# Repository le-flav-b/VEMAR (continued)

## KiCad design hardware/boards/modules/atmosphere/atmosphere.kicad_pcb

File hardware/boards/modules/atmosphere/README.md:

description of the board, maybe advice or intructions

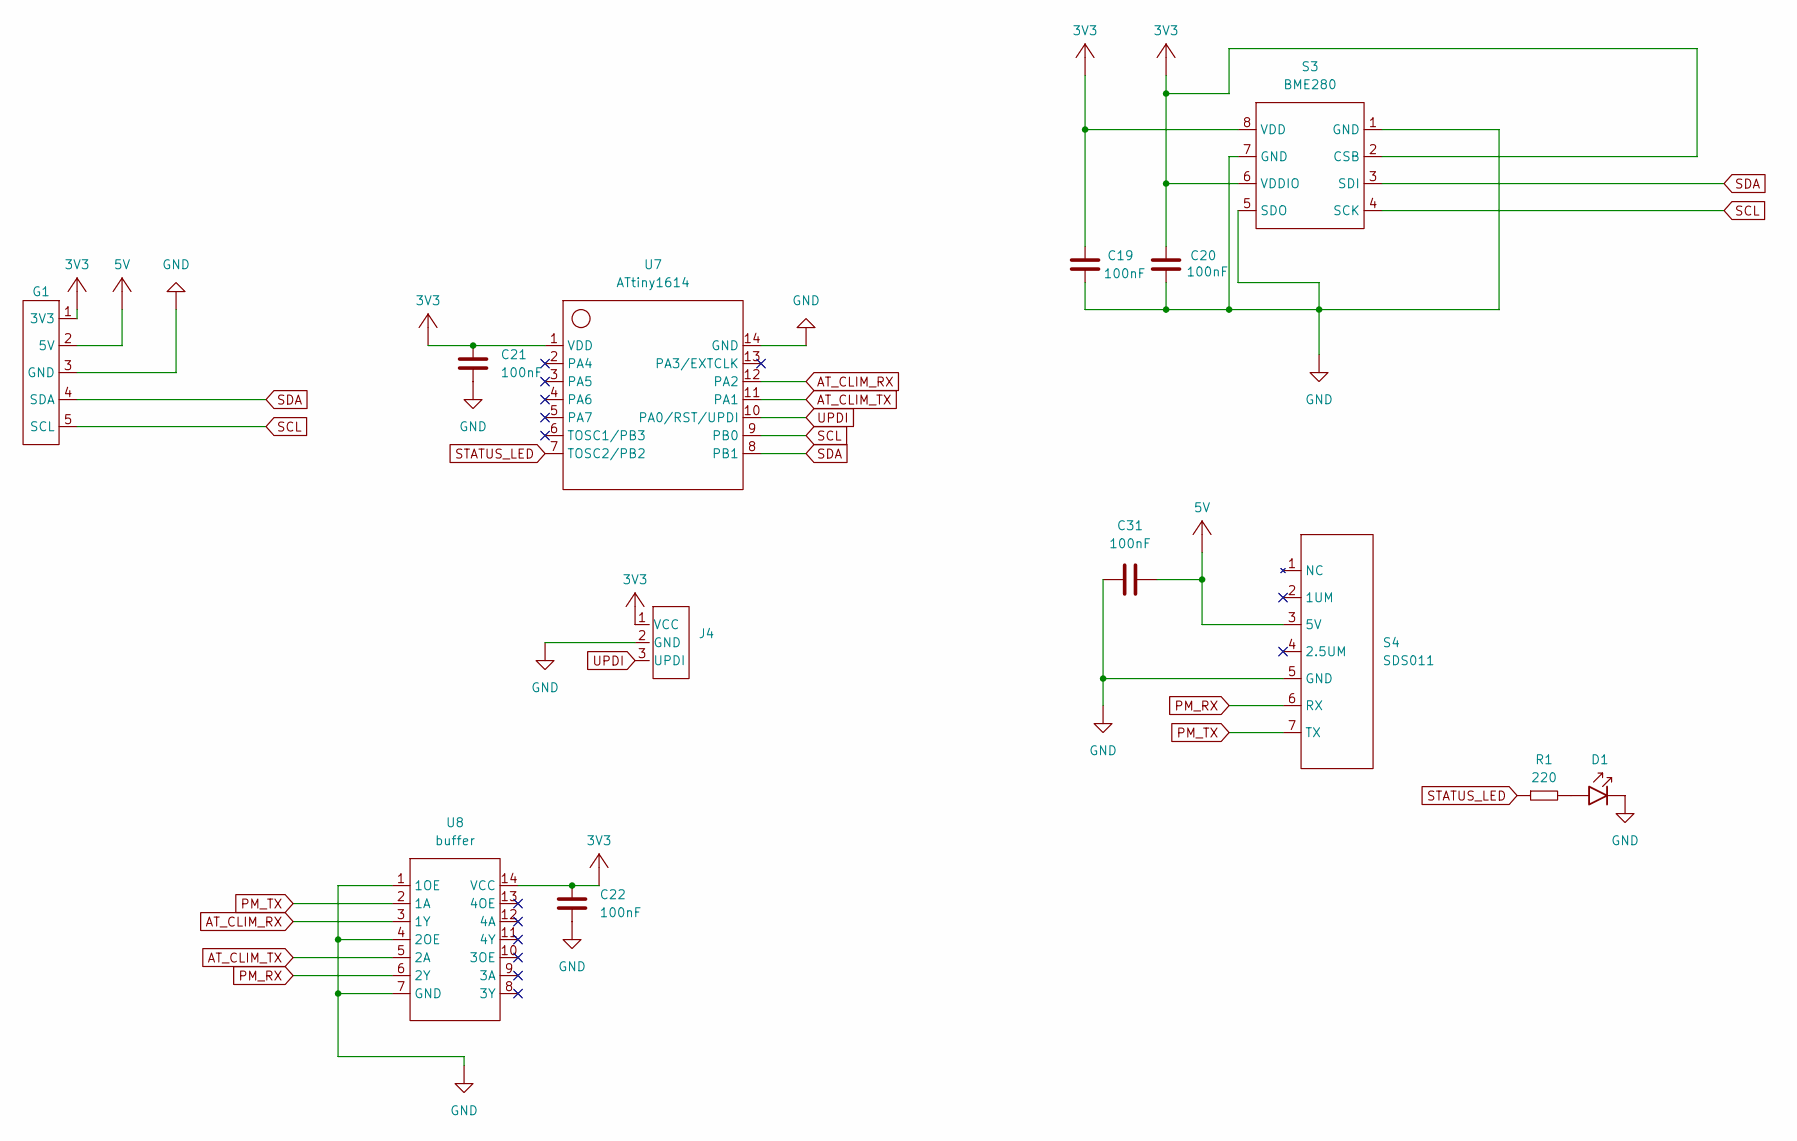
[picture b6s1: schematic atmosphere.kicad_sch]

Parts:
C19, C20, C21, C22, C31: 100nF; C_0603
D1: LED_3mm_THT
G1: GPIO_HEADER
J4: ATtiny_Programming_Header
R1: 220; R_0603
S3: BME280
S4: SDS011
U7: ATtiny1614
U8: buffer; SN74LVC125

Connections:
3V3: C19.1, C20.2, C21.2, C22.2, G1.1 (3V3), J4.1 (VCC), S3.2 (CSB), S3.6 (VDDIO), S3.8 (VDD), U7.1 (VDD), U8.14 (VCC)
5V: C31.2, G1.2 (5V), S4.3 (5V)
AT_CLIM_RX: U7.12 (PA2), U8.3 (1Y)
AT_CLIM_TX: U7.11 (PA1), U8.5 (2A)
GND: C19.2, C20.1, C21.1, C22.1, C31.1, D1.1 (K), G1.3 (GND), J4.2 (GND), S3.1 (GND), S3.5 (SDO), S3.7 (GND), S4.5 (GND), U7.14 (GND), U8.1 (1OE), U8.4 (2OE), U8.7 (GND)
unnamed: D1.2 (A), R1.2
PM_RX: S4.6 (RX), U8.6 (2Y)
PM_TX: S4.7 (TX), U8.2 (1A)
SCL: G1.5 (SCL), S3.4 (SCK), U7.9 (PB0)
SDA: G1.4 (SDA), S3.3 (SDI), U7.8 (PB1)
STATUS_LED: R1.1, U7.7 (TOSC2/PB2)
UPDI: J4.3 (UPDI), U7.10 (PA0/RST/UPDI)

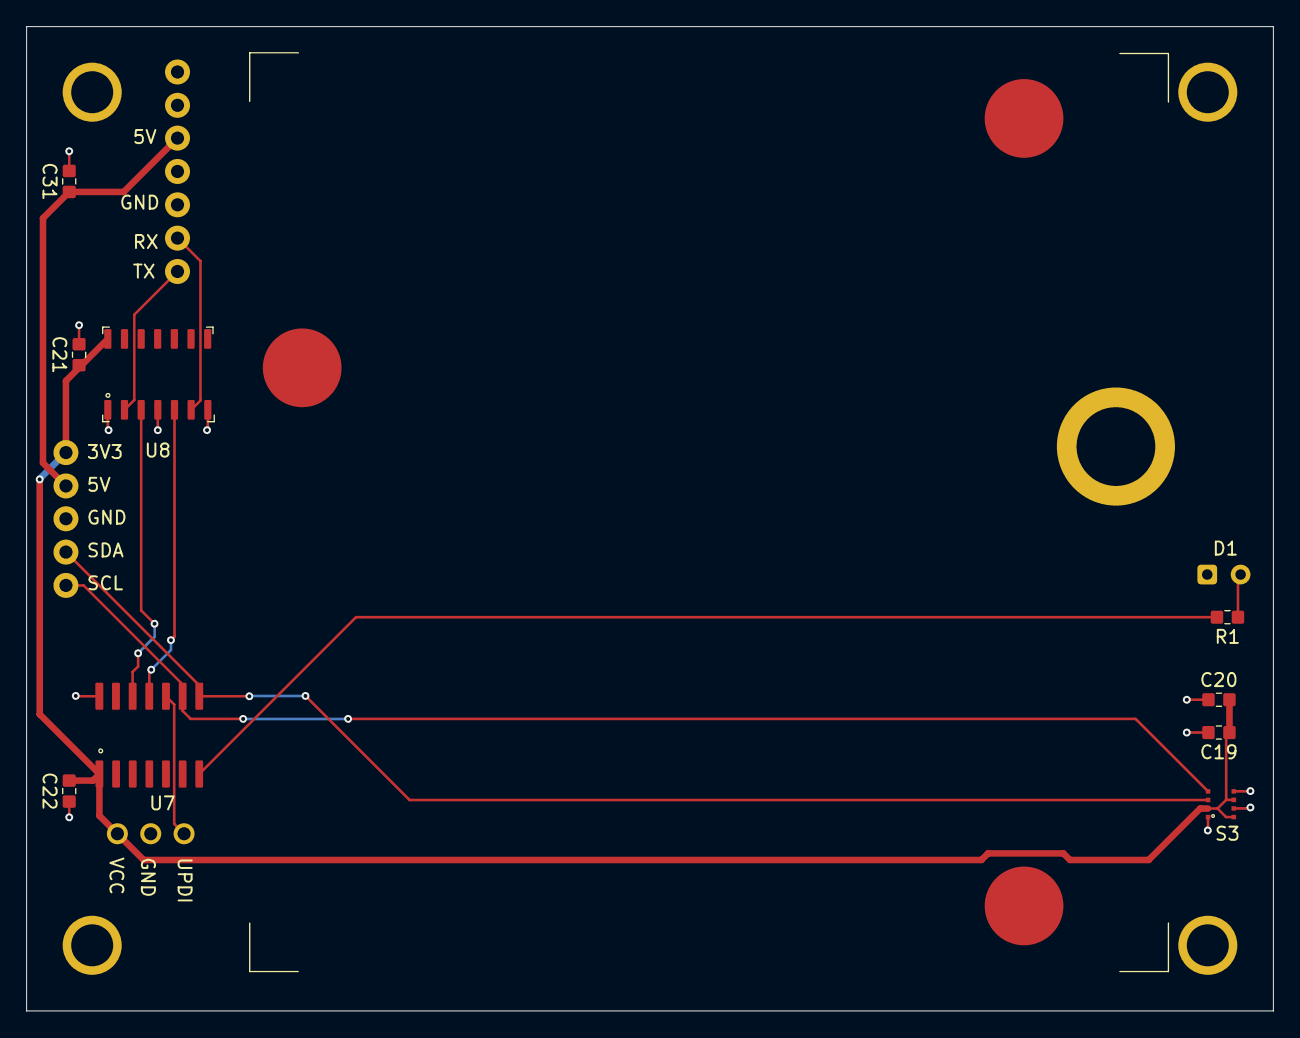
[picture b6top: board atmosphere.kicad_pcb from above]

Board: 2 copper layers, 95.0 x 75.0 mm, 13 parts (0 on the bottom side), 12 nets.

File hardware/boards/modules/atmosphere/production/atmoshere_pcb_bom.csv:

Designator,Footprint,Quantity,Value,LCSC Part #
"C19, C20, C21, C22, C31",C_0603,5,100nF,
D1,LED_3mm_THT,1,~,
G1,GPIO_HEADER,1,~,
J4,ATtiny_Programming_Header,1,~,
R1,R_0603,1,220,
S3,BME280,1,BME280,
S4,SDS011,1,SDS011,
U7,ATtiny1614,1,ATtiny1614,
U8,SN74LVC125,1,buffer,

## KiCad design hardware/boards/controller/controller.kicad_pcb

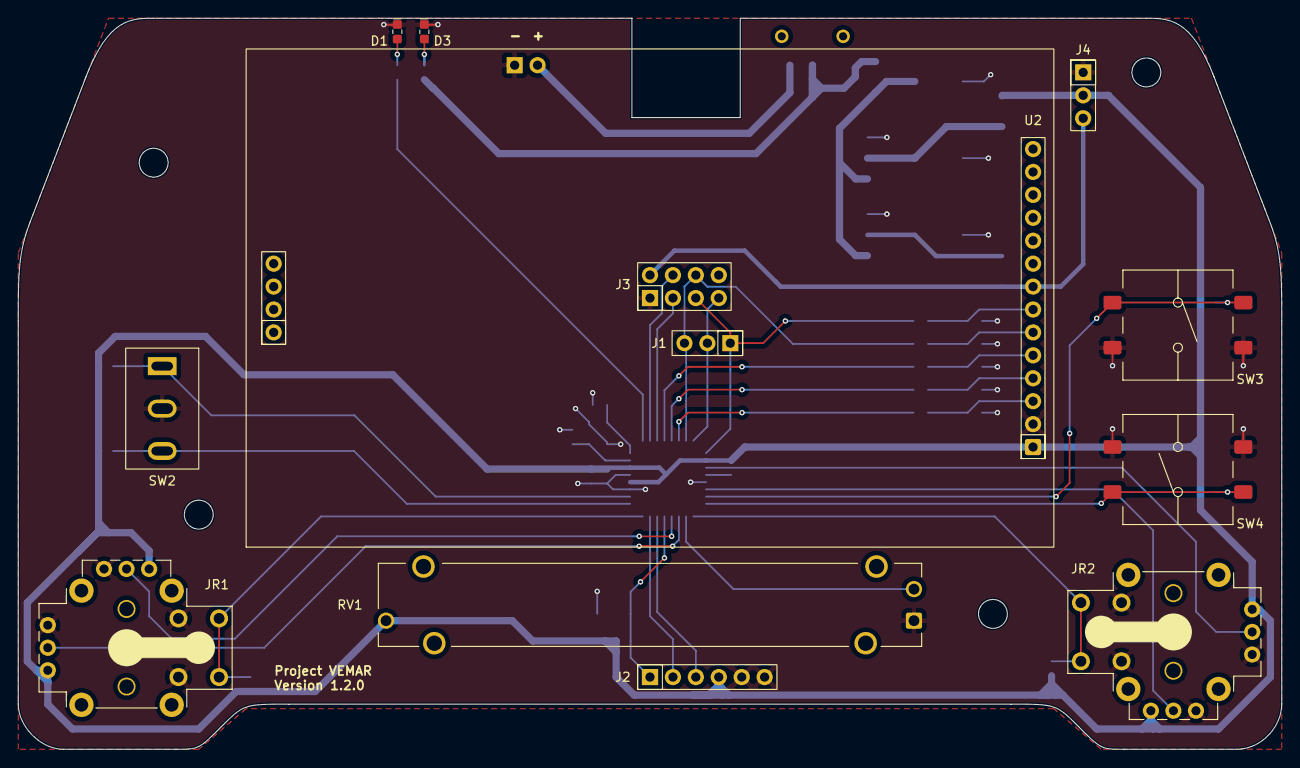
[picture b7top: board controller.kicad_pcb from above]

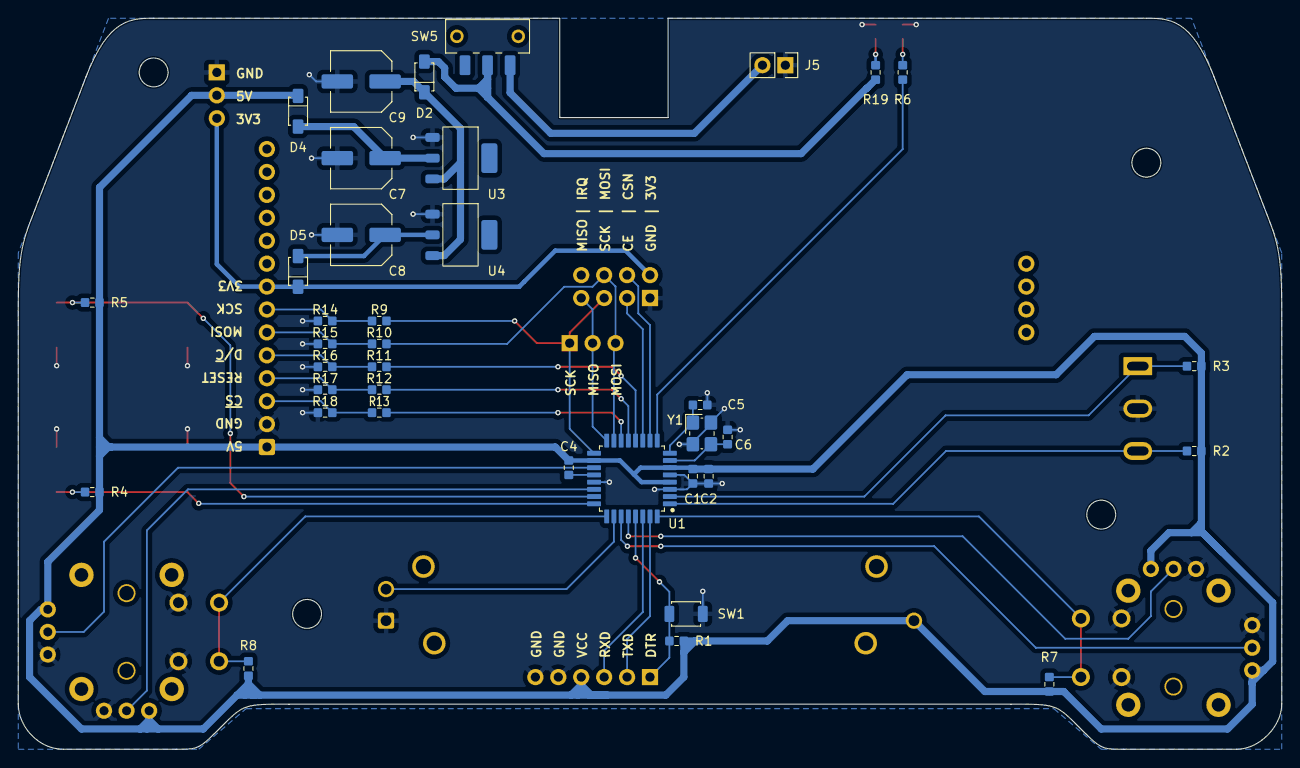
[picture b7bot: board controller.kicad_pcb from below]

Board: 2 copper layers, 140.0 x 81.0 mm, 50 parts (37 on the bottom side), 41 nets.

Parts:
C1: 1uF; C_0603
C2, C4: 100nF; C_0603
C5, C6: 12pF; C_0603
C7, C8: 22uF; C_D6.3xL5.4
C9: 100uF; C_D6.3xL5.4
D1: Green; LED_0603
D2, D4, D5: Diode; D_SOD123FL
D3: Red; LED_0603
J1, J4: 01x03; Pin_01x03
J2: 01x06; Pin_01x06
J3: 02x04; Pin_02x04
J5: 01x02; Pin_01x02
JR1, JR2: Joystick
R1, R2, R3, R4, R5, R7, R8: 10k; R_0603
R6: 330; R_0603
R9, R10, R11, R12, R13, R19: 1k; R_0603
R14, R15, R16, R17, R18: 2k; R_0603
RV1: Potentiometer; RV_45
SW1: Reset; SW_Tactile3x2.5
SW2: SW_SPDT; SW_Toggle
SW3, SW4: SW; SW_Tactile12x12
SW5: Power; SW_Slide9.1x3.5
U1: ATmega328P; ATmega328p_TQFP
U2: ILI9341
U3: AMS1117-5.0; AMS1117-SOT223
U4: AMS1117-3.3; AMS1117-SOT223
Y1: 16MHz; Crystal_3225

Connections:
+3.3V: D5.1 (K), J3.8, J4.3, U2.8 (LED)
+5V: C1.2, C2.2, C4.1, D4.1 (K), J2.4, J4.2, JR1.1 (VCC), JR1.4 (VCC), JR2.1 (VCC), JR2.4 (VCC), R1.2, R2.2, R3.2, R4.2, R5.2, R7.1, R8.2, RV1.3, U1.4 (VCC), U1.6 (VCC), U1.18 (AVCC), U2.1 (VCC)
+BATTERY: C9.1, D2.1 (K), U3.3 (VIN), U4.3 (VIN)
BTN1: R5.1, SW3.1, SW3.2, U1.23 (PC0/ADC0/PCINT8)
BTN2: R4.1, SW4.1, SW4.2, U1.24 (PC1/ADC1/PCINT9)
CE: J3.2, U1.11 (PCINT23/AIN1/PD7)
CS: R13.2, U1.14 (PCINT2/~SS/OC1B/PB2)
CSN: J3.7, U1.10 (PCINT22/OC0A/AIN0/PD6)
DC: R11.2, U1.12 (PCINT0/CLKO/ICP1/PB0)
DTR: J2.1, R1.1, SW1.2, U1.29 (PC6/~RESET/PCINT14)
GND: C1.1, C2.1, C5.1, C6.1, C7.2, C8.2, C9.2, D1.1 (K), D3.1 (K), J2.5, J2.6, J3.1, J4.1, J5.1, JR1.3 (GND), JR1.6 (GND), JR1.8 (SW2), JR1.10 (SW2), JR2.3 (GND), JR2.6 (GND), JR2.8 (SW2), JR2.10 (SW2), R14.1, R15.1, R16.1, R17.1, R18.1, RV1.1, SW1.1, SW2.2, SW3.3, SW3.4, SW4.3, SW4.4, U1.3 (GND), U1.5 (GND), U1.21 (GND), U2.2 (GND), U3.1 (GND), U4.1 (GND), Y1.2 (GND), Y1.4 (GND)
JOY1-B: JR1.7 (SW1), JR1.9 (SW1), R7.2, U1.32 (INT0/PCINT18/PD2)
JOY1-X: JR1.5 (VR2), U1.27 (PC4/ADC4/SDA/PCINT12)
JOY1-Y: JR1.2 (VR1), U1.28 (PC5/ADC5/SCL/PCINT13)
JOY2-B: JR2.7 (SW1), JR2.9 (SW1), R8.1, U1.25 (PC2/ADC2/PCINT10)
JOY2-X: JR2.2 (VR1), U1.22 (ADC7)
JOY2-Y: JR2.5 (VR2), U1.19 (ADC6)
LED: R6.2, U1.9 (PCINT21/OC0B/T1/PD5)
MISO: J1.2, J3.4, U1.16 (PCINT4/MISO/PB4)
MOSI: J1.3, J3.6, R10.2, U1.15 (PCINT3/OC2A/MOSI/PB3)
unnamed: D1.2 (A), R6.1
unnamed: D2.2 (A), R19.2, SW5.2
unnamed: D3.2 (A), R19.1
unnamed: C7.1, D4.2 (A), U3.2 (VOUT)
unnamed: C8.1, D5.2 (A), U4.2 (VOUT)
unnamed: J5.2, SW5.3
unnamed: C4.2, U1.20 (AREF)
unnamed: RV1.2, U1.26 (PC3/ADC3/PCINT11)
unnamed: C6.2, U1.7 (PCINT6/XTAL1/TOSC1/PB6), Y1.3
unnamed: C5.2, U1.8 (PCINT7/XTAL2/TOSC2/PB7), Y1.1
unnamed: R11.1, R16.2, U2.5 (D/~C)
unnamed: R10.1, R15.2, U2.6 (MOSI)
unnamed: R12.1, R17.2, U2.4 (RESET)
unnamed: R9.1, R14.2, U2.7 (SCK)
unnamed: R13.1, R18.2, U2.3 (~CS)
RESET: R12.2, U1.13 (PCINT1/OC1A/PB1)
RXD: J2.3, U1.30 (RXD/PCINT16/PD0)
SCK: J1.1, J3.3, R9.2, U1.17 (SCK/PCINT5/PB5)
TOGGLE1: R2.1, SW2.3, U1.1 (PCINT19/OC2B/INT1/PD3)
TOGGLE2: R3.1, SW2.1, U1.2 (PCINT20/XCK/T0/PD4)
TXD: J2.2, U1.31 (TXD/PCINT17/PD1)

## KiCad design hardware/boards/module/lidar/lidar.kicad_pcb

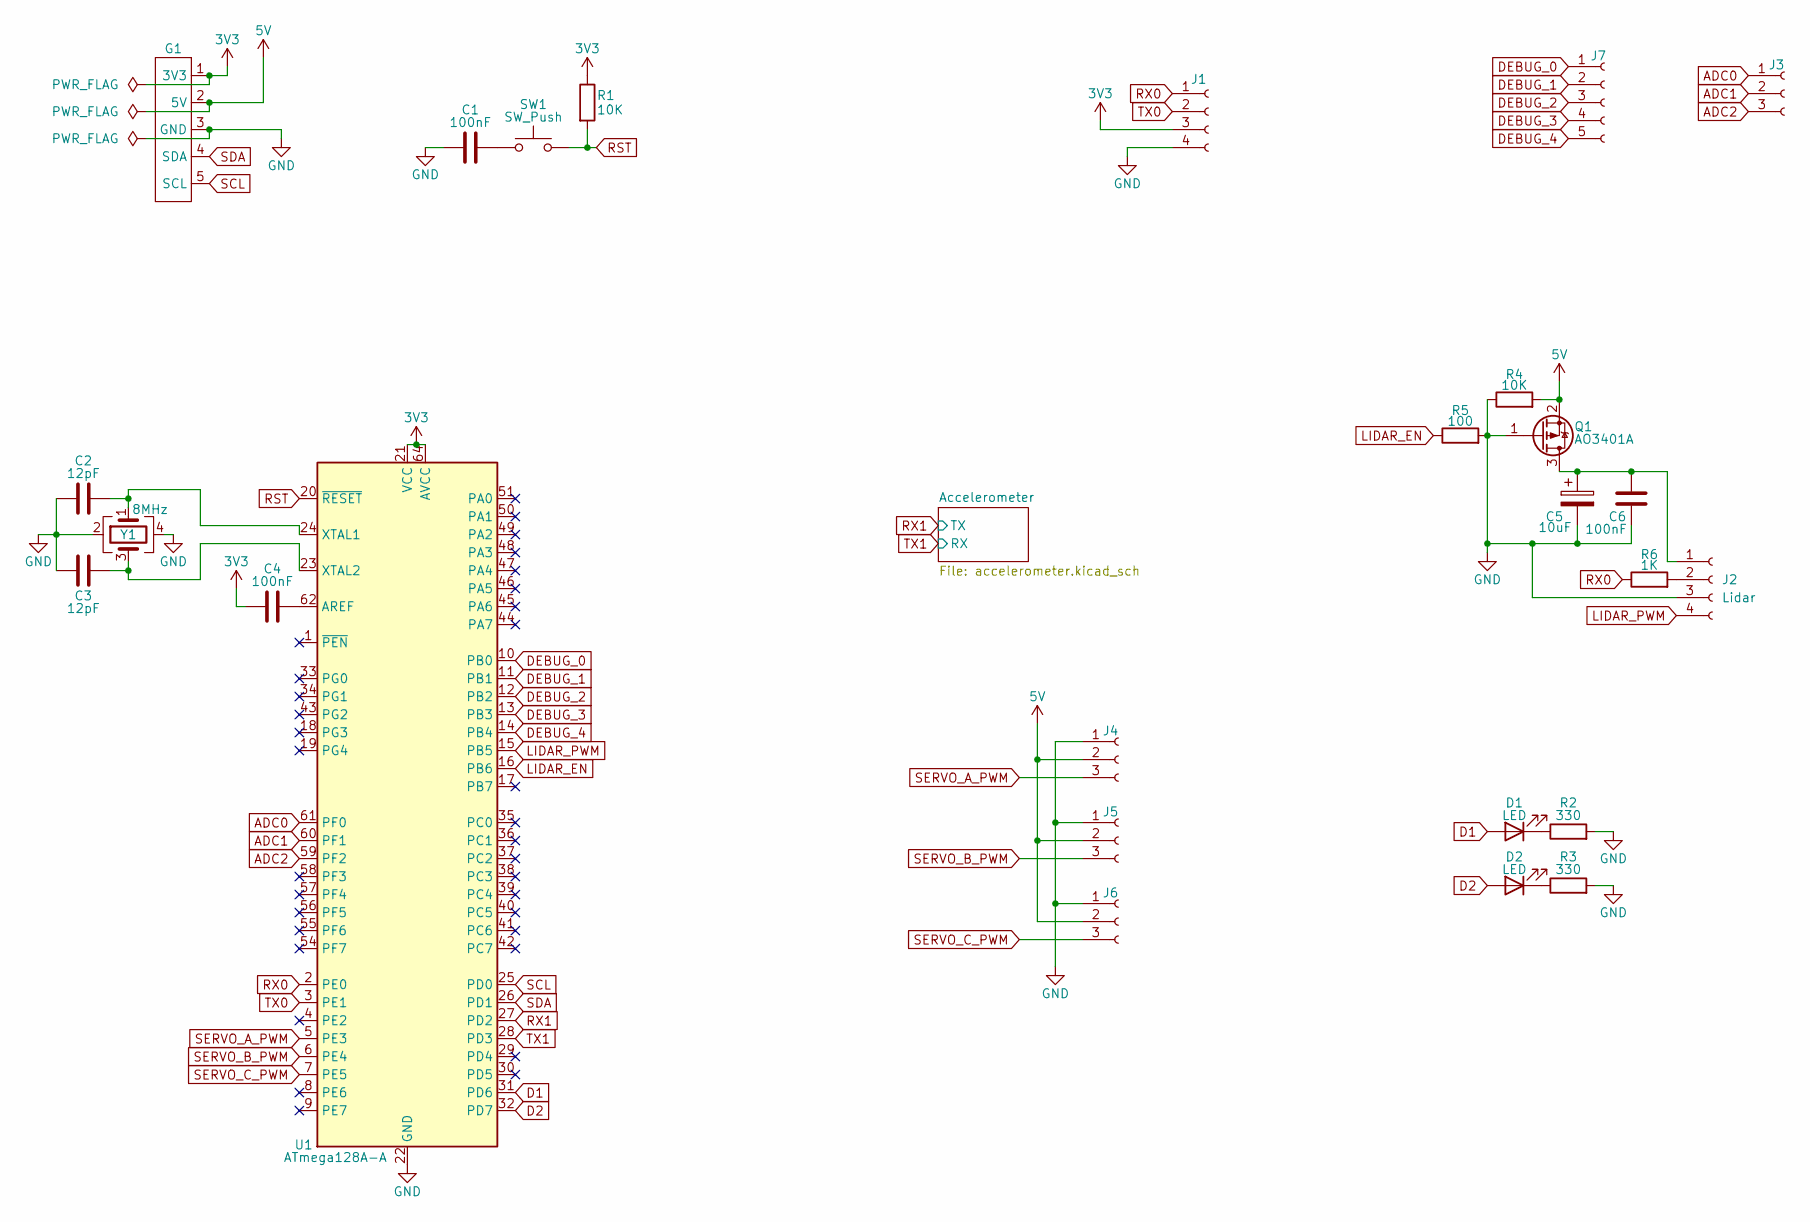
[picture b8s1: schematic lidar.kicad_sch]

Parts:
C1, C4, C6: 100nF; C_0603_1608Metric_Pad1.08x0.95mm_HandSolder
C2, C3: 12pF; C_0603_1608Metric_Pad1.08x0.95mm_HandSolder
C5: 10uF; CP_Radial_D5.0mm_P2.00mm
D1, D2: LED; LED_0603_1608Metric_Pad1.05x0.95mm_HandSolder
G1: PinHeader_1x05_P2.54mm_Vertical
J1: Conn_01x04_Socket; PinHeader_1x04_P2.54mm_Vertical
J2: Lidar; PinHeader_1x04_P2.54mm_Vertical
J3, J4, J5, J6: Conn_01x03_Socket; PinHeader_1x03_P2.54mm_Vertical
J7: Conn_01x05_Socket; PinHeader_1x05_P2.54mm_Vertical
Q1: AO3401A; SOT-23_Handsoldering
R1, R4: 10K; R_0603_1608Metric_Pad0.98x0.95mm_HandSolder
R2, R3: 330; R_0603_1608Metric_Pad0.98x0.95mm_HandSolder
R5: 100; R_0603_1608Metric_Pad0.98x0.95mm_HandSolder
R6: 1K; R_0603_1608Metric_Pad0.98x0.95mm_HandSolder
SW1: SW_Push; SW_Tactile3x2.5
U1: ATmega128A-A; TQFP-64_14x14mm_P0.8mm
Y1: 8MHz; crys_osc_smd3225_4

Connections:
3V3: C4.1, G1.1 (3V3), J1.3, R1.1, U1.21 (VCC), U1.52 (VCC), U1.64 (AVCC); also elsewhere on the board
5V: G1.2 (5V), J4.2, J5.2, J6.2, Q1.2 (S), R4.2
ADC0: J3.1, U1.61 (PF0)
ADC1: J3.2, U1.60 (PF1)
ADC2: J3.3, U1.59 (PF2)
D1: D1.2 (A), U1.31 (PD6)
D2: D2.2 (A), U1.32 (PD7)
DEBUG_0: J7.1, U1.10 (PB0)
DEBUG_1: J7.2, U1.11 (PB1)
DEBUG_2: J7.3, U1.12 (PB2)
DEBUG_3: J7.4, U1.13 (PB3)
DEBUG_4: J7.5, U1.14 (PB4)
GND: C1.1, C2.2, C3.2, C5.2, C6.2, G1.3 (GND), J1.4, J2.3, J4.1, J5.1, J6.1, Q1.1 (G), R2.2, R3.2, R4.1, R5.2, U1.22 (GND), U1.53 (GND), U1.63 (GND), Y1.2, Y1.4; also elsewhere on the board
LIDAR_EN: R5.1, U1.16 (PB6)
LIDAR_PWM: J2.4, U1.15 (PB5)
unnamed: C1.2, SW1.1
unnamed: D1.1 (K), R2.1
unnamed: D2.1 (K), R3.1
unnamed: C5.1, C6.1, J2.1, Q1.3 (D)
unnamed: J2.2, R6.2
unnamed: C4.2, U1.62 (AREF)
unnamed: C2.1, U1.24 (XTAL1), Y1.1
unnamed: C3.1, U1.23 (XTAL2), Y1.3
RST: R1.2, SW1.2, U1.20 (~RESET)
RX0: J1.1, R6.1, U1.2 (PE0)
RX1: U1.27 (PD2); also elsewhere on the board
SCL: G1.5 (SCL), U1.25 (PD0)
SDA: G1.4 (SDA), U1.26 (PD1)
SERVO_A_PWM: J4.3, U1.5 (PE3)
SERVO_B_PWM: J5.3, U1.6 (PE4)
SERVO_C_PWM: J6.3, U1.7 (PE5)
TX0: J1.2, U1.3 (PE1)
TX1: U1.28 (PD3); also elsewhere on the board

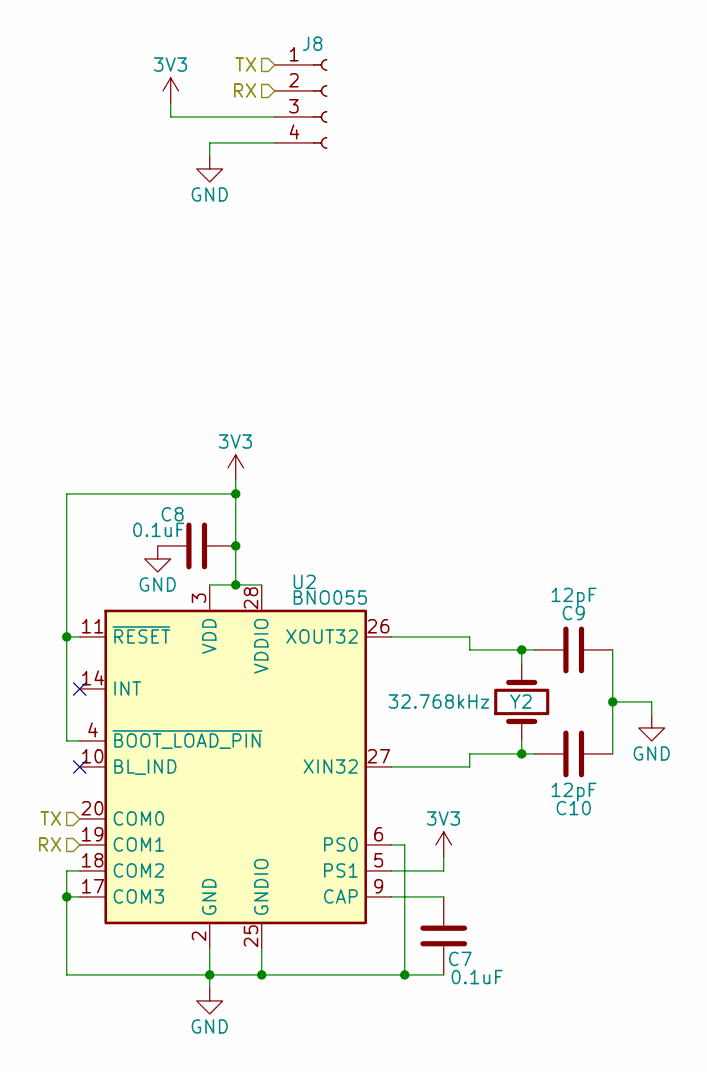
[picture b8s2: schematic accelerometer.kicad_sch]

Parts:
C7, C8: 0.1uF; C_0603_1608Metric_Pad1.08x0.95mm_HandSolder
C9, C10: 12pF; C_0603_1608Metric_Pad1.08x0.95mm_HandSolder
J8: Conn_01x04_Socket; PinHeader_1x04_P2.54mm_Vertical
U2: BNO055; BNO055_Hand_Soldering_LGA-28_5.2x3.8mm_P0.5mm
Y2: 32.768kHz; Crystal_SMD_3215-2Pin_3.2x1.5mm

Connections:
3V3: C8.2, J8.3, U2.3 (VDD), U2.4 (~BOOT_LOAD_PIN), U2.5 (PS1), U2.11 (~RESET), U2.28 (VDDIO); also elsewhere on the board
GND: C7.2, C8.1, C9.2, C10.2, J8.4, U2.2 (GND), U2.6 (PS0), U2.17 (COM3), U2.18 (COM2), U2.25 (GNDIO); also elsewhere on the board
unnamed: C7.1, U2.9 (CAP)
unnamed: C10.1, U2.27 (XIN32), Y2.1
unnamed: C9.1, U2.26 (XOUT32), Y2.2
RX1: J8.1, U2.20 (COM0); also elsewhere on the board
TX1: J8.2, U2.19 (COM1); also elsewhere on the board

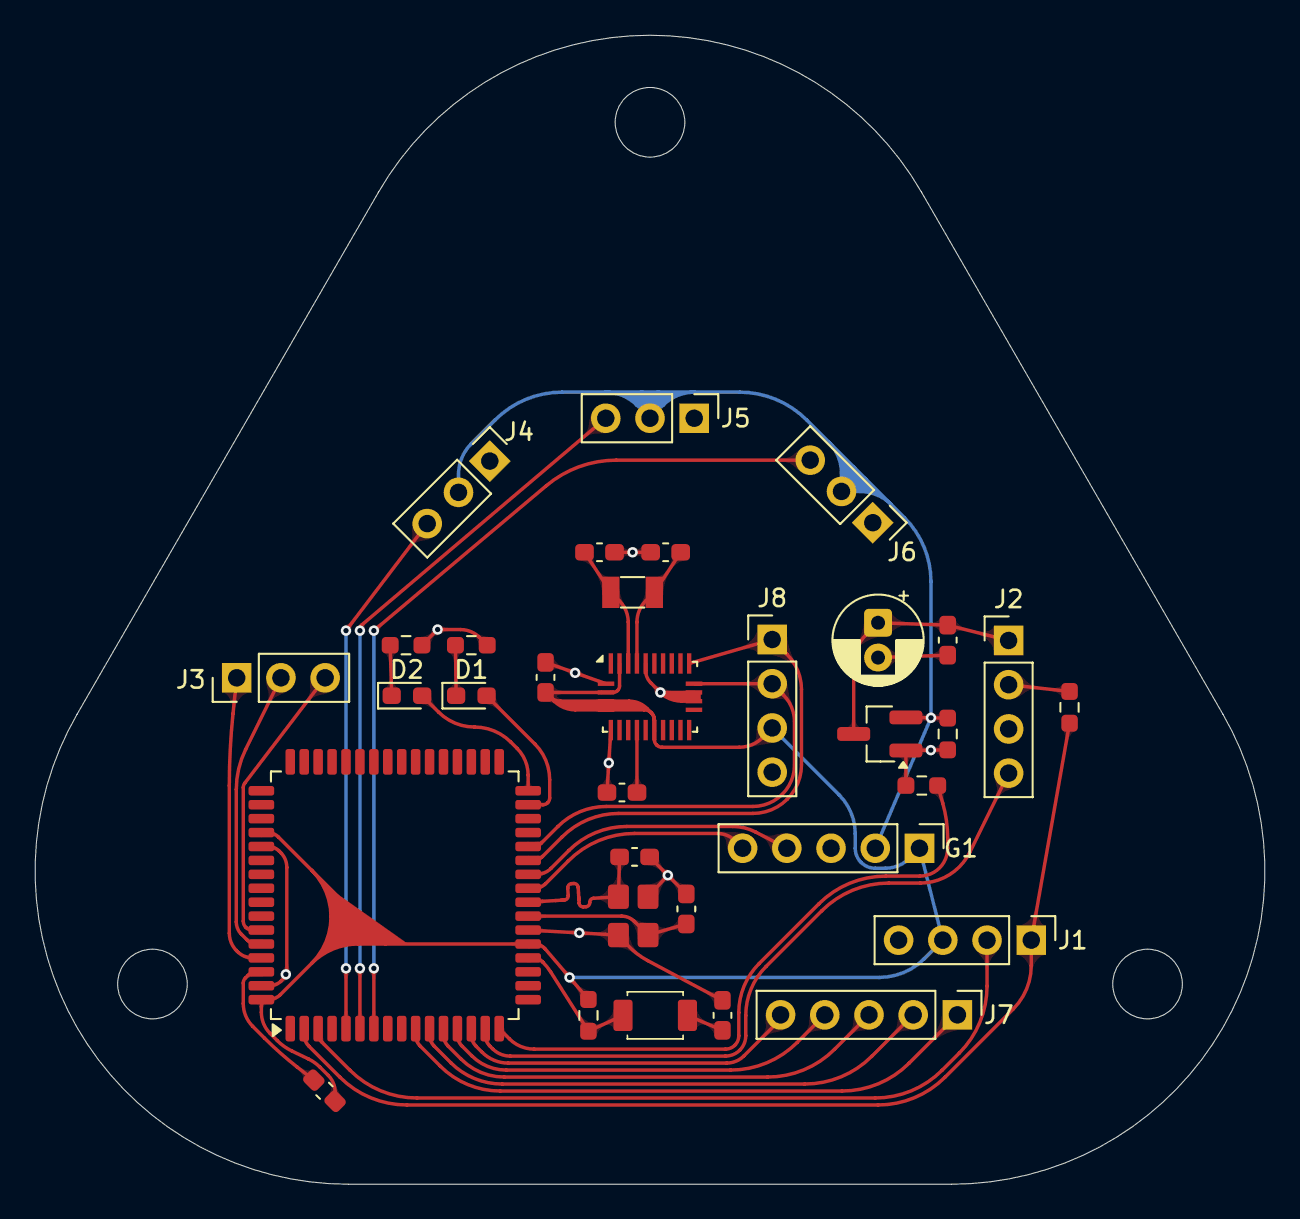
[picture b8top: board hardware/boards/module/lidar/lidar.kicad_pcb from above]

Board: 2 copper layers, 70.6 x 66.0 mm, 33 parts (0 on the bottom side), 36 nets.

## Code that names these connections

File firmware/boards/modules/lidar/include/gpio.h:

#ifndef GPIO_H
# define GPIO_H

typedef struct {
	volatile uint8_t	*ddr;
	volatile uint8_t	*port;
	volatile uint8_t	*pin;
	uint8_t				bit;
}					gpio_t;

# define _PA0 ((gpio_t){&DDRA, &PORTA, &PINA, PA0})
# define _PA1 ((gpio_t){&DDRA, &PORTA, &PINA, PA1})
# define _PA2 ((gpio_t){&DDRA, &PORTA, &PINA, PA2})
# define _PA3 ((gpio_t){&DDRA, &PORTA, &PINA, PA3})
# define _PA4 ((gpio_t){&DDRA, &PORTA, &PINA, PA4})
# define _PA5 ((gpio_t){&DDRA, &PORTA, &PINA, PA5})
# define _PA6 ((gpio_t){&DDRA, &PORTA, &PINA, PA6})
# define _PA7 ((gpio_t){&DDRA, &PORTA, &PINA, PA7})

# define _PB0 ((gpio_t){&DDRB, &PORTB, &PINB, PB0})
# define _PB1 ((gpio_t){&DDRB, &PORTB, &PINB, PB1})
# define _PB2 ((gpio_t){&DDRB, &PORTB, &PINB, PB2})
# define _PB3 ((gpio_t){&DDRB, &PORTB, &PINB, PB3})
# define _PB4 ((gpio_t){&DDRB, &PORTB, &PINB, PB4})
# define _PB5 ((gpio_t){&DDRB, &PORTB, &PINB, PB5})
# define _PB6 ((gpio_t){&DDRB, &PORTB, &PINB, PB6})
# define _PB7 ((gpio_t){&DDRB, &PORTB, &PINB, PB7})

# define _PC0 ((gpio_t){&DDRC, &PORTC, &PINC, PC0})
# define _PC1 ((gpio_t){&DDRC, &PORTC, &PINC, PC1})
# define _PC2 ((gpio_t){&DDRC, &PORTC, &PINC, PC2})
# define _PC3 ((gpio_t){&DDRC, &PORTC, &PINC, PC3})
# define _PC4 ((gpio_t){&DDRC, &PORTC, &PINC, PC4})
# define _PC5 ((gpio_t){&DDRC, &PORTC, &PINC, PC5})
# define _PC6 ((gpio_t){&DDRC, &PORTC, &PINC, PC6})
# define _PC7 ((gpio_t){&DDRC, &PORTC, &PINC, PC7})

# define _PD0 ((gpio_t){&DDRD, &PORTD, &PIND, PD0})
# define _PD1 ((gpio_t){&DDRD, &PORTD, &PIND, PD1})
# define _PD2 ((gpio_t){&DDRD, &PORTD, &PIND, PD2})
# define _PD3 ((gpio_t){&DDRD, &PORTD, &PIND, PD3})
# define _PD4 ((gpio_t){&DDRD, &PORTD, &PIND, PD4})
# define _PD5 ((gpio_t){&DDRD, &PORTD, &PIND, PD5})
# define _PD6 ((gpio_t){&DDRD, &PORTD, &PIND, PD6})
# define _PD7 ((gpio_t){&DDRD, &PORTD, &PIND, PD7})

# define _PE0 ((gpio_t){&DDRE, &PORTE, &PINE, PE0})
# define _PE1 ((gpio_t){&DDRE, &PORTE, &PINE, PE1})
# define _PE2 ((gpio_t){&DDRE, &PORTE, &PINE, PE2})
# define _PE3 ((gpio_t){&DDRE, &PORTE, &PINE, PE3})
# define _PE4 ((gpio_t){&DDRE, &PORTE, &PINE, PE4})
# define _PE5 ((gpio_t){&DDRE, &PORTE, &PINE, PE5})
# define _PE6 ((gpio_t){&DDRE, &PORTE, &PINE, PE6})
# define _PE7 ((gpio_t){&DDRE, &PORTE, &PINE, PE7})

# define _PF0 ((gpio_t){&DDRF, &PORTF, &PINF, PF0})
# define _PF1 ((gpio_t){&DDRF, &PORTF, &PINF, PF1})
# define _PF2 ((gpio_t){&DDRF, &PORTF, &PINF, PF2})
# define _PF3 ((gpio_t){&DDRF, &PORTF, &PINF, PF3})
# define _PF4 ((gpio_t){&DDRF, &PORTF, &PINF, PF4})
# define _PF5 ((gpio_t){&DDRF, &PORTF, &PINF, PF5})
# define _PF6 ((gpio_t){&DDRF, &PORTF, &PINF, PF6})
# define _PF7 ((gpio_t){&DDRF, &PORTF, &PINF, PF7})

# define _PG0 ((gpio_t){&DDRG, &PORTG, &PING, PG0})
# define _PG1 ((gpio_t){&DDRG, &PORTG, &PING, PG1})
# define _PG2 ((gpio_t){&DDRG, &PORTG, &PING, PG2})
# define _PG3 ((gpio_t){&DDRG, &PORTG, &PING, PG3})
# define _PG4 ((gpio_t){&DDRG, &PORTG, &PING, PG4})
# define _PG5 ((gpio_t){&DDRG, &PORTG, &PING, PG5})
# define _PG6 ((gpio_t){&DDRG, &PORTG, &PING, PG6})
# define _PG7 ((gpio_t){&DDRG, &PORTG, &PING, PG7})

#endif

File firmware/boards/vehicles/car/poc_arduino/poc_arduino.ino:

#define PIN_M1_EN_CW 7
#define PIN_M1_EN_CCW 8
#define PIN_M1_PWM_CW 5
#define PIN_M1_PWM_CCW 6

#define PIN_M2_EN_CW 14
#define PIN_M2_EN_CCW 15
#define PIN_M2_PWM_CW 9
#define PIN_M2_PWM_CCW 10


void setup() {
  pinMode(PIN_M1_EN_CW, OUTPUT);
  pinMode(PIN_M1_EN_CCW, OUTPUT);
  pinMode(PIN_M1_PWM_CW, OUTPUT);
  pinMode(PIN_M1_PWM_CCW, OUTPUT);

  pinMode(PIN_M2_EN_CW, OUTPUT);
  pinMode(PIN_M2_EN_CCW, OUTPUT);
  pinMode(PIN_M2_PWM_CW, OUTPUT);
  pinMode(PIN_M2_PWM_CCW, OUTPUT);

  off();
}

void off() {
  digitalWrite(PIN_M1_EN_CW, LOW);
  digitalWrite(PIN_M1_PWM_CW, LOW);
  digitalWrite(PIN_M1_EN_CCW, LOW);
  digitalWrite(PIN_M1_PWM_CCW, LOW);
  digitalWrite(PIN_M2_EN_CW, LOW);
  digitalWrite(PIN_M2_PWM_CW, LOW);
  digitalWrite(PIN_M2_EN_CCW, LOW);
  digitalWrite(PIN_M2_PWM_CCW, LOW);
  delay(2);
}


void on() {
  digitalWrite(PIN_M1_EN_CW, HIGH);
  analogWrite(PIN_M1_PWM_CW, 255);
  digitalWrite(PIN_M2_EN_CW, HIGH);
  analogWrite(PIN_M2_PWM_CW, 255);
}

void loop() {
  digitalWrite(PIN_M1_EN_CW, HIGH);
  analogWrite(PIN_M1_PWM_CW, 100);
  digitalWrite(PIN_M2_EN_CW, HIGH);
  analogWrite(PIN_M2_PWM_CW, 100);
  delay(5000);

  off();
  delay(2000);

  digitalWrite(PIN_M1_EN_CW, HIGH);
  analogWrite(PIN_M1_PWM_CW, 255);
  digitalWrite(PIN_M2_EN_CW, HIGH);
  analogWrite(PIN_M2_PWM_CW, 255);
  delay(5000);

  off();
  delay(2000);

  digitalWrite(PIN_M1_EN_CCW, HIGH);
  analogWrite(PIN_M1_PWM_CCW, 100);
  digitalWrite(PIN_M2_EN_CCW, HIGH);
  analogWrite(PIN_M2_PWM_CCW, 100);
  delay(5000);

  off();
  delay(2000);

  digitalWrite(PIN_M1_EN_CCW, HIGH);
  analogWrite(PIN_M1_PWM_CCW, 255);
  digitalWrite(PIN_M2_EN_CCW, HIGH);
  analogWrite(PIN_M2_PWM_CCW, 255);
  delay(5000);

  off();
  delay(2000);
}

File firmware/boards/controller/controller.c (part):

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{
    g_controller.tgl.up = BUTTON_new(PIN_TOGGLE_UP, BUTTON_ONHOLD);
    g_controller.tgl.down = BUTTON_new(PIN_TOGGLE_DOWN, BUTTON_ONHOLD);
    g_controller.btn1 = BUTTON_new(PIN_BUTTON1, BUTTON_ONPRESS);
    g_controller.btn2 = BUTTON_new(PIN_BUTTON2, BUTTON_ONPRESS);
    g_controller.pot = ANALOG_new(PIN_POTENTIOMETER);
    g_controller.jright = JOYSTICK_new(PIN_JOY_RX, PIN_JOY_RY, PIN_JOY_RB);
    g_controller.jleft = JOYSTICK_new(PIN_JOY_LX, PIN_JOY_LY, PIN_JOY_LB);
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void CONTROLLER_interrupt(void)
{
    BIT_set(PCICR, (BIT(PCIE1) | BIT(PCIE2)));      // enable interrupt (Port C & D)
    BIT_set(PCMSK1, (BIT(PCINT8) | BIT(PCINT9)));   // enable PC0 and PC1
    BIT_set(PCMSK2, (BIT(PCINT19) | BIT(PCINT20))); // enable PD3 and PD4
    sei();
}

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                _CONTROLLER_switch_display();
            }
        }
    } // PC0 interrupt

    if (BIT_is_clear(PINC, BIT(PINC1)))
    {
        g_save_toggle = TRUE;
    } // PC1 interrupt
}

//------------------------------------------------------------------------------
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
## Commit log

2025-12-01 project structure
2025-12-01 added Makefile for firmware
2025-12-14 adding air sensor schemas
2025-12-15 specifications
2026-01-09 add source code for controller
2026-01-09 feat(controller): add Makefile
2026-01-09 fix(controller): fix register
2026-01-11 feat(controller): add spi
2026-01-12 update library
2026-01-13 feat(controller): update documentation
2026-01-20 added some code from prototyping
2026-01-22 feat(symbol): symbol library
2026-01-22 update controller schematics
2026-01-23 controller schematics updated
2026-01-24 adding ignore rule for backups
2026-01-24 updated schema
    added 5V 3A buck converter
    refined 3v3 LDO
    added symbols for new components
    added text comments for designing the pcb
2026-01-25 vehicle schematic
2026-01-25 poc for lidar and accelerometer
2026-01-25 new kicad project for lidar module
2026-01-26 fix(controller): tag CE <-> PD6
2026-01-27 feat(controller): add 3d models
2026-01-27 feat(footprint): add footprint
2026-01-27 feat(pcb): pcb wip
2026-01-28 removing backups and adding footprints for sensors and power components
2026-01-28 minor edit to symbols, removing unused attiny symbols
2026-01-29 updated power symbol labels, replaced power symbols in schematic with our own custom symbols
2026-01-29 feat(pcb): working pcb design
2026-01-29 feat(schematic): cleanup controller
2026-01-30 feat(footprint): add 0805 package footprint
2026-01-30 added pcb for gas and climate modules
2026-01-30 deleted backups
2026-01-31 added status LED to gas module
2026-01-31 added status LED to climate module
2026-02-01 lidar schematic
2026-02-01 car schematic
2026-02-01 add BOM
2026-02-01 added sensor modules to bom
2026-02-01 added 1206 smd capacitor footprint
2026-02-02 add resistor 330Ohm, capacitor 1nF
2026-02-02 update controller pcb
2026-02-02 archive gerber files
2026-02-02 added all footprints for lidar and car
2026-02-02 lidar pcb
2026-02-02 car schema updated
2026-02-03 updated pcb after DRC
2026-02-03 update gerber file
2026-02-03 rounded tracks on lidar pcb
2026-02-03 corrected SD card and transceiver on symbol and schema
2026-02-03 added teardrops to lidar pcb
2026-02-03 added gerber files for climate and gas module
2026-02-03 rename file
2026-02-03 moved gerber of controller to Gerber_Files
2026-02-03 zipped my gerbs
2026-02-04 pcb for car
2026-02-04 gerber file
2026-02-04 edited inductor footprint for car and export gerber for lidar
2026-02-04 add functions for gpio
2026-02-05 redid gerber zips for modules
2026-02-06 rename print -> serial
2026-02-06 removed cause path changed
2026-02-09 rework joystick
2026-02-09 add more examples
2026-02-09 fix include file
2026-02-11 specify hex number width
2026-02-13 new module: nrf24l01
2026-02-17 update on lidar and car kicad project
2026-02-17 fix issue with transceiver
2026-02-18 REFACTO of all the repo to stick to the planed architecture, STILL NEED to re link everything
2026-02-18 REFACTO relinked every kicad projects
2026-02-23 started mechanical design for lidar module, bearing and servo f3d files
2026-02-23 added lidar and motor f3d files
2026-02-25 updated servomotor f3d file with another arm
2026-02-25 added lidar f3d file with pivot component
2026-02-25 create architecture for mechanical/export folder with the lidar pivot_frame file
2026-02-25 updated servomotor model so we can cut support and gain place
2026-02-26 radio bidirectional communication
2026-03-03 update adc/analog & add docs
2026-03-04 update uart/spi and add docs
2026-03-05 fix duplicate definition
2026-03-06 basic functions for display characters
2026-03-09 tft display string
2026-03-10 init for i2c lib
2026-03-10 include twi header
2026-03-11 add attiny pack & fix issues with makefile
2026-03-13 updated master and fixed minor errors
2026-03-18 modify pins of examples
2026-03-19 update docs for tft
2026-03-19 adding geiger schema
2026-03-20 cleanup files & update docs
2026-03-20 finished geiger module pcb
2026-03-24 added missing status LED to radioactivity board
2026-03-24 redesigned gas module pcb
2026-03-25 restarting lib
2026-03-25 added wait helper functions
2026-03-25 populated interrupt, check msg len
2026-03-25 added missing nack
2026-03-25 changed nack to ack for empty buffer, reset message index on interrupt
2026-04-01 added code for bme280 sensor
2026-04-01 started atmosphere module code
2026-04-01 added code to switch from slave to master
2026-04-02 update libraries: footprint, symbols and 3D models
2026-04-02 new version for pcb controller
2026-04-03 add utilities for timer & pwm
2026-04-07 updated makefile, atmosphere header, bme and i2c
2026-04-07 fix screen orientation
2026-04-08 add controller gerber file
2026-04-08 added code for gasses module
2026-04-08 updated atmosphere slave
2026-04-09 add main controller folder
2026-04-09 added pocs to lidar firmware
2026-04-09 added pocs to car firmware
2026-04-09 updated main points of the lidar module schematic
2026-04-09 updated main points of the car schematic
2026-04-13 car PCB
2026-04-13 added teardrops to lidar and car PCB, should be good
2026-04-13 added production files for lidar and car PCB
2026-04-15 upgraded makefile of lidar module firmware
2026-04-16 fix i2c read
2026-04-16 updated sensor module schematics
2026-04-16 pre-merge commit to save progress
2026-04-16 updated symbols and schemas with new symbols
2026-04-16 add kicad transceiver module
2026-04-16 i2c reading 0 values
2026-04-16 added multiple wakeups
2026-04-16 move files to libraries
2026-04-16 added debugging data
2026-04-17 started sd library
2026-04-17 first iteration sd lib
2026-04-18 lidar code refacto
2026-04-18 firmware structure and base for lidar and car
2026-04-19 added low level control for motors in car firmware
2026-04-19 removed arduino poc
2026-04-19 updated header
2026-04-20 corrected buzzer code on car firmware
2026-04-20 communication between gas module and controller
2026-04-22 added interactive bom for lidar and car
2026-04-23 rework pinout
2026-04-24 adc value from -255 to 255
2026-04-28 car firmware h bridge working
2026-04-28 ability to switch between sensor
2026-04-28 example communication car
2026-04-28 add packet structure
2026-04-28 pushing current code for chris
2026-04-28 atmosphere uart working
2026-04-29 firmware car
2026-04-29 update controller
2026-04-29 current working code for sensor modules
2026-04-29 updated i2c init
2026-04-30 updated i2c lib
2026-04-30 updated sd library
2026-04-30 added arduino example code
2026-04-30 communication controller <-> atmosphere sensor
2026-04-30 added example geiger counter master ino
2026-04-30 communication controller <-> geiger
2026-05-01 cleanup code
2026-05-01 update packet format
2026-05-01 explicit conversion from pwm to pin
2026-05-01 add file gas.c
2026-05-01 moved files to car/src
2026-05-01 remove folder vehicle/sensors
2026-05-01 saving current data logging implementation
2026-05-02 improve module dectection
2026-05-02 atmosphere module now inits bme
2026-05-02 added preheat time
2026-05-02 added geiger makefile
2026-05-02 added geiger header
2026-05-02 added bme init flag sent to master, slave no longer inits
2026-05-02 fixed indices mismatch for gas readings
2026-05-02 fix phantom packet
2026-05-02 fixed sd save implementation
2026-05-03 able to send command to record to sd card
2026-05-03 added sd save var to controller packet and b button press toggles it
2026-05-03 removed unneeded function call
2026-05-03 added save toggling to data_save to prevent sd corruption
2026-05-03 added debounce to save button and updated data save (still not working)
2026-05-03 add first draft of main README
2026-05-03 removed sd close on fail
2026-05-03 added radio pause for sd to write
2026-05-03 added mising cast to space var
2026-05-03 added motor ramp up and down to prevent current spikes
2026-05-03 added checks for atmega128a
2026-05-04 change kicad default to custom
2026-05-04 lidar pass to ESP32
2026-05-04 lidar firmware esp32 v1
2026-05-04 add function itoa_decimal2
2026-05-04 car firmware for lidar dont work
2026-05-04 removing unused stdstring
2026-05-04 removing pinouts
2026-05-04 tidied comments
2026-05-07 lidar final poc
